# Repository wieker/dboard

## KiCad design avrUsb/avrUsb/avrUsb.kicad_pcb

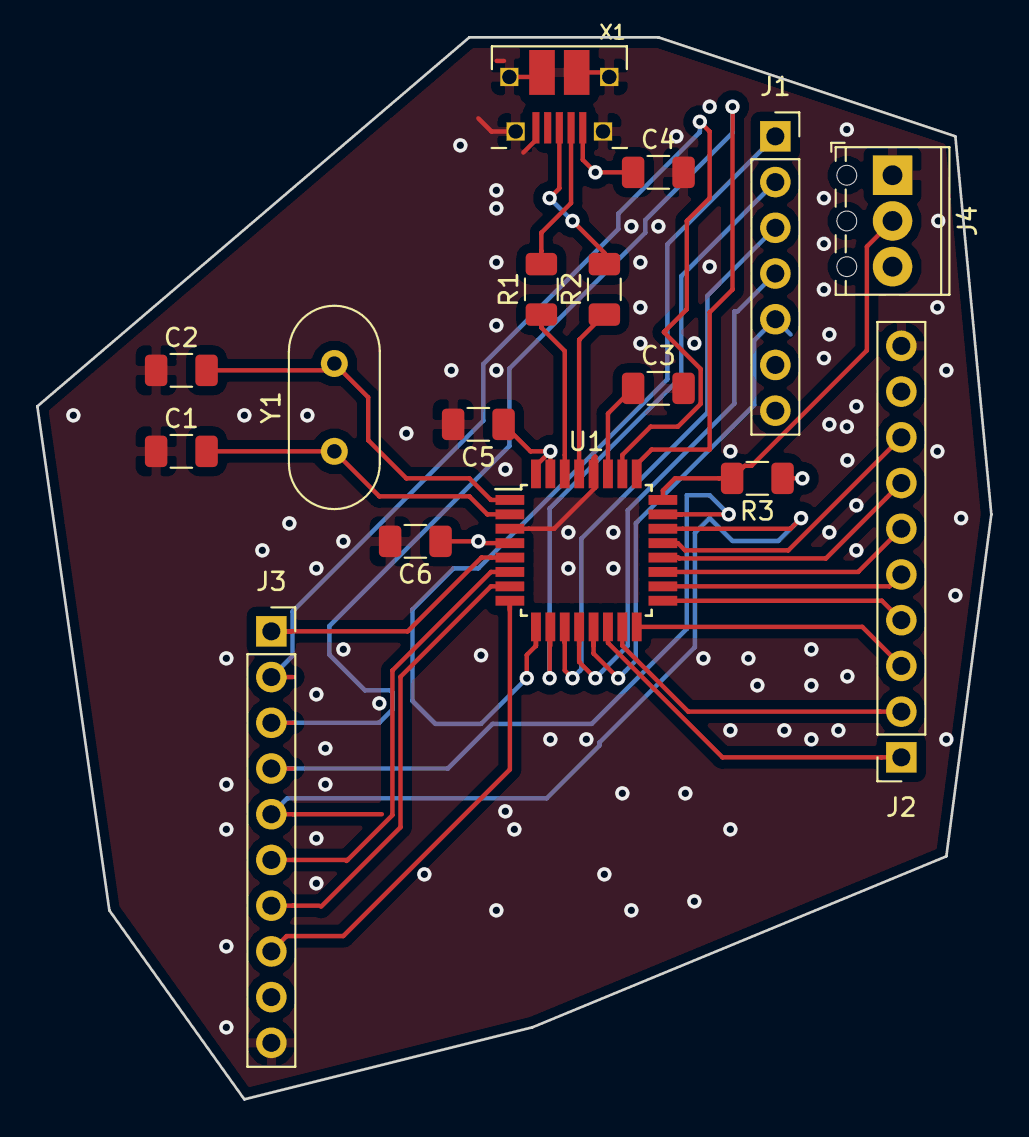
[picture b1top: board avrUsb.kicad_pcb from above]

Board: 4 copper layers, 53.0 x 59.0 mm, 16 parts (0 on the bottom side), 31 nets.

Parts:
C1, C2: 20p; C_1206_3216Metric
C3: 1uF; C_1206_3216Metric
C4: 10uF; C_1206_3216Metric
C5, C6: 100nF; C_1206_3216Metric
J1: Screw_Terminal_01x07; PinSocket_1x07_P2.54mm_Vertical
J2, J3: Screw_Terminal_01x10; PinSocket_1x10_P2.54mm_Vertical
J4: Screw_Terminal_01x03; TerminalBlock_Phoenix_MPT-0,5-3-2.54_1x03_P2.54mm_Horizontal
R1, R2: 22; R_1206_3216Metric
R3: 10k; R_1206_3216Metric
U1: ATmega32U2-MU; TQFP-32_7x7mm_P0.8mm
X1: USBFCI_10103594; FCI_10103594_MILL
Y1: 8 Mhz; Crystal_HC49-U_Vertical

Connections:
GND: C1.1, C2.1, C3.2, C4.2, C5.2, C6.2, J1.7, J2.10, J3.10, J4.1, U1.3, U1.28, X1.BASE@1, X1.BASE@2, X1.GND, X1.SPRT@1, X1.SPRT@2, X1.SPRT@3, X1.SPRT@4
unnamed: C1.2, U1.2, Y1.1
unnamed: C2.2, U1.1, Y1.2
unnamed: C3.1, U1.27
unnamed: J1.1, U1.9
unnamed: J1.2, U1.10
unnamed: J1.3, U1.11
unnamed: J1.4, U1.12
unnamed: J1.5, U1.13
unnamed: J2.1, U1.14
unnamed: J2.2, U1.15
unnamed: J2.3, U1.16
unnamed: J2.4, U1.17
unnamed: J2.5, U1.18
unnamed: J2.6, U1.19
unnamed: J2.7, U1.20
unnamed: J2.8, U1.21
unnamed: J3.1, U1.5
unnamed: J3.2, U1.26
unnamed: J3.3, U1.25
unnamed: J3.4, U1.23
unnamed: J3.5, U1.22
unnamed: J3.6, U1.6
unnamed: J3.7, U1.7
unnamed: J3.8, U1.8
unnamed: J4.2, R3.2, U1.24
unnamed: R1.1, U1.30
unnamed: R1.2, X1.D-
unnamed: R2.1, U1.29
unnamed: R2.2, X1.D+
VCC: C4.1, C5.1, C6.1, J1.6, J2.9, J3.9, J4.3, R3.1, U1.4, U1.31, U1.32, X1.VBUS

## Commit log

2019-05-23 updated usb polarity + reset header
